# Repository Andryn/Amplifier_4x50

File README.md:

# Amplifier_4x50
Amplifier 4x50W KiCad hardware project (TDA7560  and similar)

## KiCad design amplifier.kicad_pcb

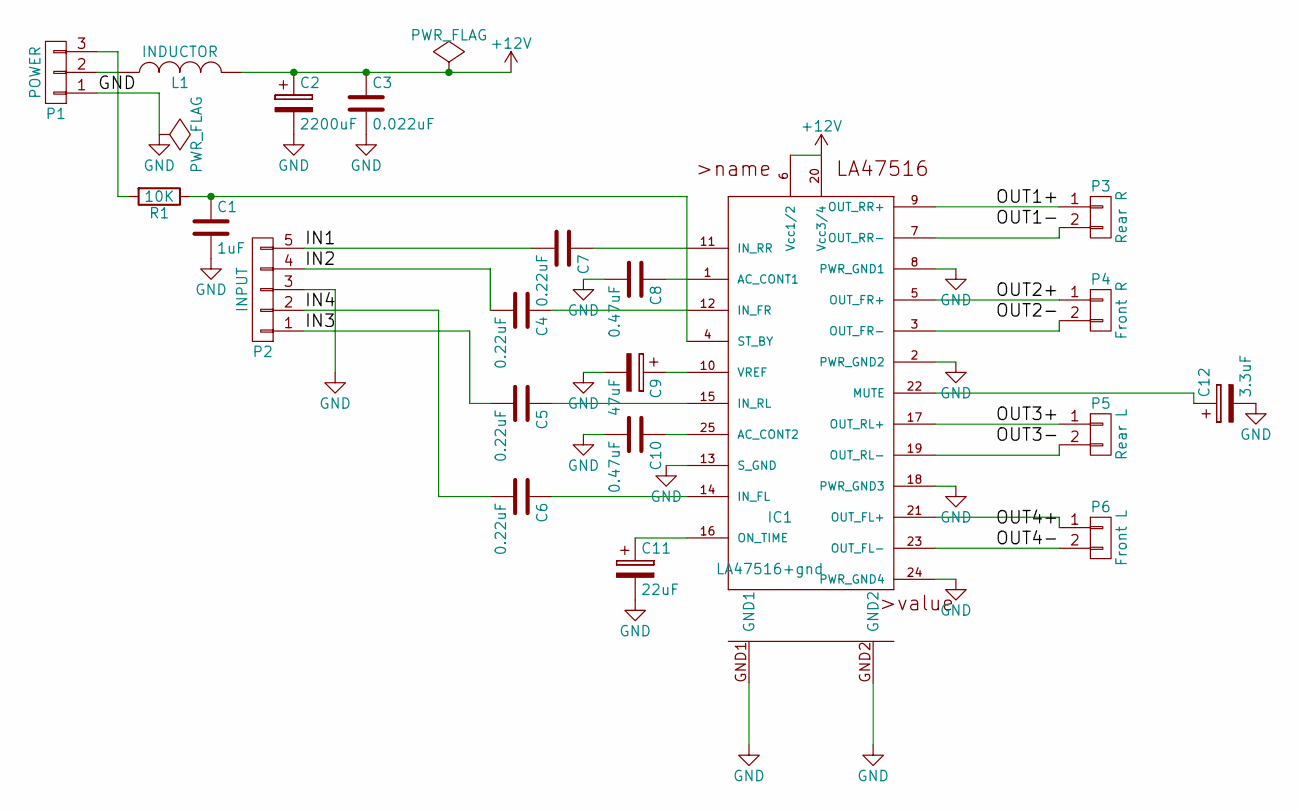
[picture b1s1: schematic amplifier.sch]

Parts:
C1: 1uF; C_Disc_D6_P5
C2: 2200uF; C_Radial_D10_L25_P5
C3: 0.022uF; C_Disc_D6_P5
C4, C5, C6, C7: 0.22uF; C_Disc_D6_P5
C8, C10: 0.47uF; C_Disc_D6_P5
C9: 47uF; C_Radial_D5_L6_P2.5
C11: 22uF; C_Radial_D5_L6_P2.5
C12: 3.3uF; C_Radial_D5_L6_P2.5
IC1: LA47516+gnd; HZIP25_2.0+GND
L1: INDUCTOR; Inducror
P1: POWER; bornier3
P2: INPUT; bornier5
P3: Rear R; bornier2
P4: Front R; bornier2
P5: Rear L; bornier2
P6: Front L; bornier2
R1: 10K; Resistor_Vertical_RM5mm

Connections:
+12V: C2.1, C3.1, IC1.6 (Vcc1/2), IC1.20 (Vcc3/4), L1.2
/IN1: C7.2, P2.5
/IN2: C4.2, P2.4
/IN3: C5.2, P2.1
/IN4: C6.2, P2.2
/OUT1+: IC1.9 (OUT_RR+), P3.1
/OUT1-: IC1.7 (OUT_RR-), P3.2
/OUT2+: IC1.5 (OUT_FR+), P4.1
/OUT2-: IC1.3 (OUT_FR-), P4.2
/OUT3+: IC1.17 (OUT_RL+), P5.1
/OUT3-: IC1.19 (OUT_RL-), P5.2
/OUT4+: IC1.21 (OUT_FL+), P6.1
/OUT4-: IC1.23 (OUT_FL-), P6.2
GND: C1.2, C2.2, C3.2, C8.2, C9.2, C10.2, C11.2, C12.2, IC1.2 (PWR_GND2), IC1.8 (PWR_GND1), IC1.13 (S_GND), IC1.18 (PWR_GND3), IC1.24 (PWR_GND4), IC1.GND1, IC1.GND2, P1.1, P2.3
unnamed: C1.1, IC1.4 (ST_BY), R1.1
unnamed: C4.1, IC1.12 (IN_FR)
unnamed: C5.1, IC1.15 (IN_RL)
unnamed: C6.1, IC1.14 (IN_FL)
unnamed: C7.1, IC1.11 (IN_RR)
unnamed: C8.1, IC1.1 (AC_CONT1)
unnamed: C9.1, IC1.10 (VREF)
unnamed: C10.1, IC1.25 (AC_CONT2)
unnamed: C11.1, IC1.16 (ON_TIME)
unnamed: C12.1, IC1.22 (MUTE)
unnamed: L1.1, P1.2
unnamed: P1.3, R1.2

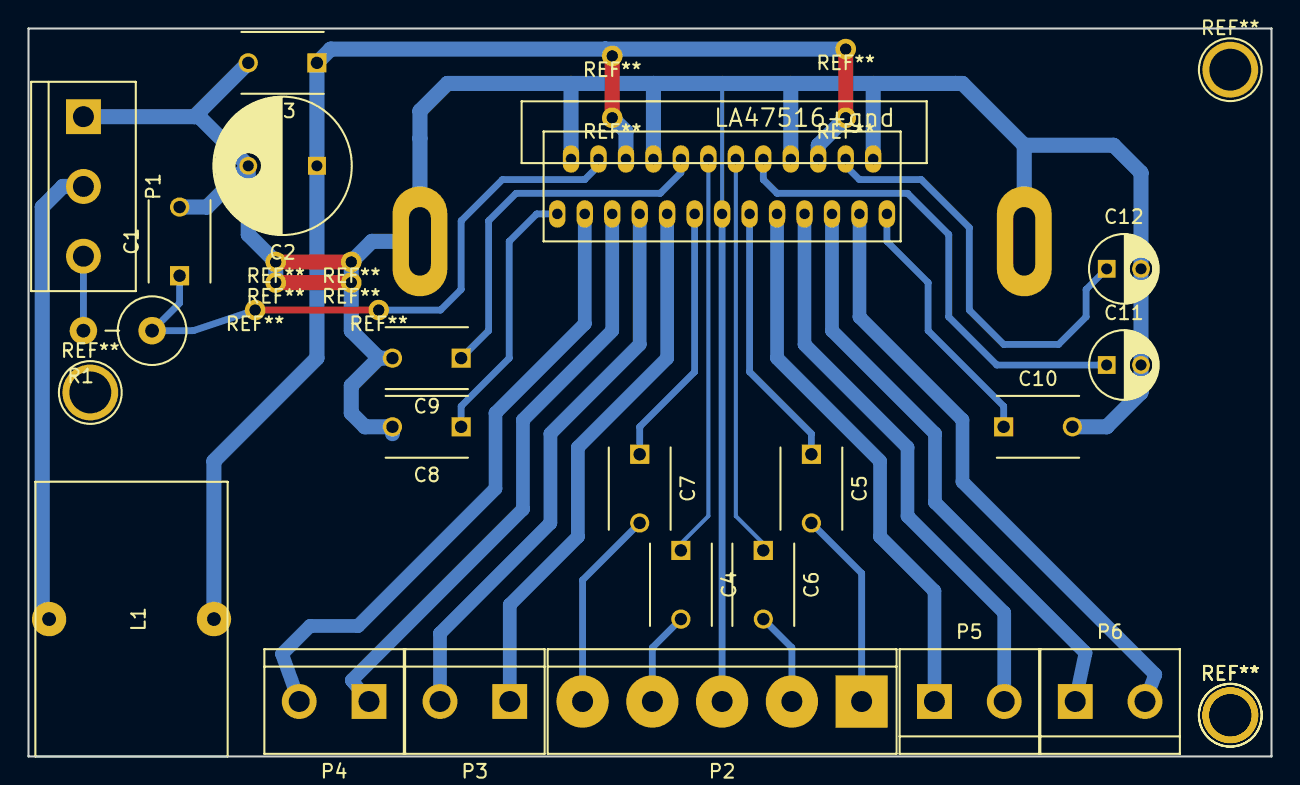
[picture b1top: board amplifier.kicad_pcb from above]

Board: 2 copper layers, 90.5 x 53.0 mm, 21 parts (0 on the bottom side), 26 nets.

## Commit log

2016-04-15 :space_invader: Added .gitattributes & .gitignore files
2016-04-15 Add images and Open SCAD files for box
